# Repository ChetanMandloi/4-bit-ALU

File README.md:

# 4-bit-ALU
A simple design to perform basic logical operations (such as logical AND, OR, NOT, Addition, Subtraction and Multiplication) on two 4 bit variables using DIY PCB fabrication and assembly methods.

KiCad files to allow you to make a 4 bit ALU using Double sided copper clad board.
Pictures and instructions incoming soon.

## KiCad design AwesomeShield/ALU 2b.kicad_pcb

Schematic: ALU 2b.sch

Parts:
BT1: Battery_Cell; Pin_Header_Straight_1x02_Pitch2.54mm
D1, D2, D3, D4, D5, D6, D7, D8, D9, D10, D11, D12, D13, D14, D15, D16, D17, D18, D19, D20, D21, D22, D23, D24, D25, D26, D27, D28, D29, D30, D31, D32, D33, D34, D35: LED; LED_1206
J1, J2, J6: CONN_01X04; Pin_Header_Straight_1x04_Pitch2.54mm
J3: CONN_01X03; Pin_Header_Straight_1x03_Pitch2.54mm
J4: CONN_01X08; Pin_Header_Straight_1x08_Pitch2.54mm
J5: CONN_01X01; Pin_Header_Straight_1x01_Pitch2.54mm
R1, R2, R3, R4, R5, R6, R7, R8, R9, R10, R11, R12, R13, R14, R15, R16, R17, R18, R19, R20, R21, R22, R23, R24, R25, R26, R28: R; R_1206
U1, U2, U3: 74LS08; DIP-14_W7.62mm_Socket_LongPads
U4, U5, U6: 74LS83; DIP-16_W7.62mm_Socket_LongPads
U7: 74LS244; DIP-20_W7.62mm_Socket_LongPads
U8, U9, U10: LM741; DIP-8_W7.62mm_Socket_LongPads

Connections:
/Control_Pin_from_Board_1: U6.15, U7.15
/Data_A: BT1.2 (-), D1.1 (K), D2.1 (K), D3.1 (K), D4.1 (K), D5.1 (K), D6.1 (K), D7.1 (K), D8.1 (K), D9.1 (K), D10.1 (K), D11.1 (K), D20.1 (K), D21.1 (K), D22.1 (K), D23.1 (K), D24.1 (K), D25.1 (K), D26.1 (K), D27.1 (K), R20.2, R21.2, R22.2, R23.2, R24.2, R25.2, R26.2, R28.2, U1.7, U2.7, U3.7, U4.12, U5.12, U6.12, U7.10
unnamed: BT1.1 (+), D12.2 (A), D13.2 (A), D14.2 (A), D15.2 (A), D16.2 (A), D17.2 (A), D18.2 (A), D19.2 (A), D28.2 (A), D29.2 (A), D30.2 (A), D31.2 (A), D32.2 (A), D33.2 (A), D34.2 (A), D35.2 (A), U1.14, U2.14, U3.14, U4.5, U5.5, U6.5, U7.20, U8.1, U8.2 (-), U8.3 (+), U8.4 (V-), U9.1, U9.2 (-), U9.3 (+), U9.4 (V-), U10.2 (-), U10.3 (+), U10.4 (V-)
unnamed: D1.2 (A), D12.1 (K), R1.2
unnamed: D9.2 (A), R5.2
unnamed: D10.2 (A), R6.2
unnamed: D11.2 (A), R7.2
unnamed: D2.2 (A), D13.1 (K), R2.2
unnamed: D3.2 (A), D14.1 (K), R3.2
unnamed: D4.2 (A), D15.1 (K), R4.2
unnamed: D5.2 (A), D16.1 (K), R8.2
unnamed: D6.2 (A), D17.1 (K), R9.2
unnamed: D7.2 (A), D18.1 (K), R10.2
unnamed: D8.2 (A), D19.1 (K), R11.2
unnamed: D20.2 (A), D28.1 (K), R19.2
unnamed: D21.2 (A), D29.1 (K), R18.2
unnamed: D22.2 (A), D30.1 (K), R17.2
unnamed: D23.2 (A), D31.1 (K), R16.2
unnamed: D24.2 (A), D32.1 (K), R15.2
unnamed: D25.2 (A), D33.1 (K), R14.2
unnamed: D26.2 (A), D34.1 (K), R13.2
unnamed: D27.2 (A), D35.1 (K), R12.2
unnamed: J1.1, R4.1, R23.1, U1.13, U2.10, U3.5, U8.5
unnamed: J1.2, R3.1, R22.1, U1.2, U2.13, U3.10, U8.6
unnamed: J1.3, R2.1, R21.1, U1.5, U2.2, U3.13, U8.7 (V+)
unnamed: J1.4, R1.1, R20.1, U1.10, U2.5, U3.2, U8.8 (NC)
unnamed: J2.1, R11.1, R28.1, U1.1, U1.4, U1.9, U9.5
unnamed: J2.2, R10.1, R26.1, U1.12, U2.1, U2.4, U9.6
unnamed: J2.3, R9.1, R25.1, U2.9, U2.12, U3.1, U9.7 (V+)
unnamed: J2.4, R8.1, R24.1, U3.4, U3.9, U3.12, U9.8 (NC)
unnamed: J3.1, R5.1, U10.7 (V+)
unnamed: J3.2, R6.1, U10.6
unnamed: J3.3, R7.1, U10.5
unnamed: J4.1, R12.1, U7.18
unnamed: J4.2, R13.1, U7.16
unnamed: J4.3, R14.1, U7.14
unnamed: J4.4, R15.1, U7.12
unnamed: J4.5, R16.1, U7.9
unnamed: J4.6, R17.1, U7.7
unnamed: J4.7, R18.1, U7.5
unnamed: J4.8, R19.1, U7.3
unnamed: J5.1, U7.1, U7.19
unnamed: J6.1, U7.2
unnamed: J6.2, U4.7
unnamed: J6.3, U5.4
unnamed: J6.4, U6.16
unnamed: U1.3, U4.10
unnamed: U1.6, U4.8
unnamed: U1.8, U4.3
unnamed: U1.11, U4.11
unnamed: U2.3, U4.4
unnamed: U2.6, U4.16
unnamed: U2.8, U5.11
unnamed: U2.11, U5.7
unnamed: U3.3, U5.16
unnamed: U3.6, U6.11
unnamed: U3.8, U6.7
unnamed: U3.11, U6.4
unnamed: U4.1, U4.13, U5.13, U6.13
unnamed: U4.2, U5.8
unnamed: U4.6, U5.10
unnamed: U4.9, U7.4
unnamed: U4.14, U5.1
unnamed: U4.15, U5.3
unnamed: U5.2, U6.8
unnamed: U5.6, U6.10
unnamed: U5.9, U7.6
unnamed: U5.14, U6.1
unnamed: U5.15, U6.3
unnamed: U6.2, U7.13
unnamed: U6.6, U7.11
unnamed: U6.9, U7.8
unnamed: U6.14, U7.17

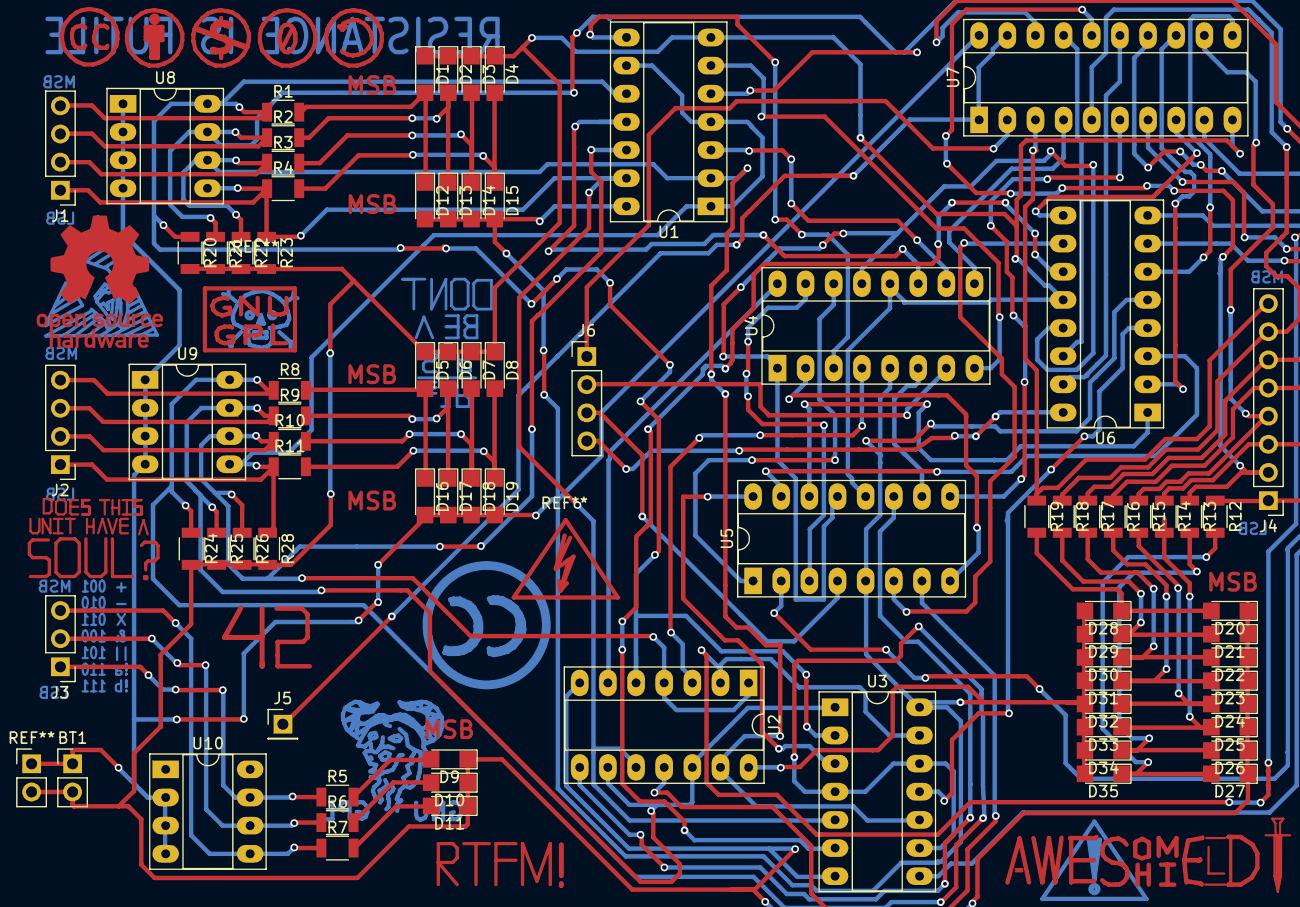
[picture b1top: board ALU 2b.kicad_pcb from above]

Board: 2 copper layers, 79 parts (0 on the bottom side), 73 nets.

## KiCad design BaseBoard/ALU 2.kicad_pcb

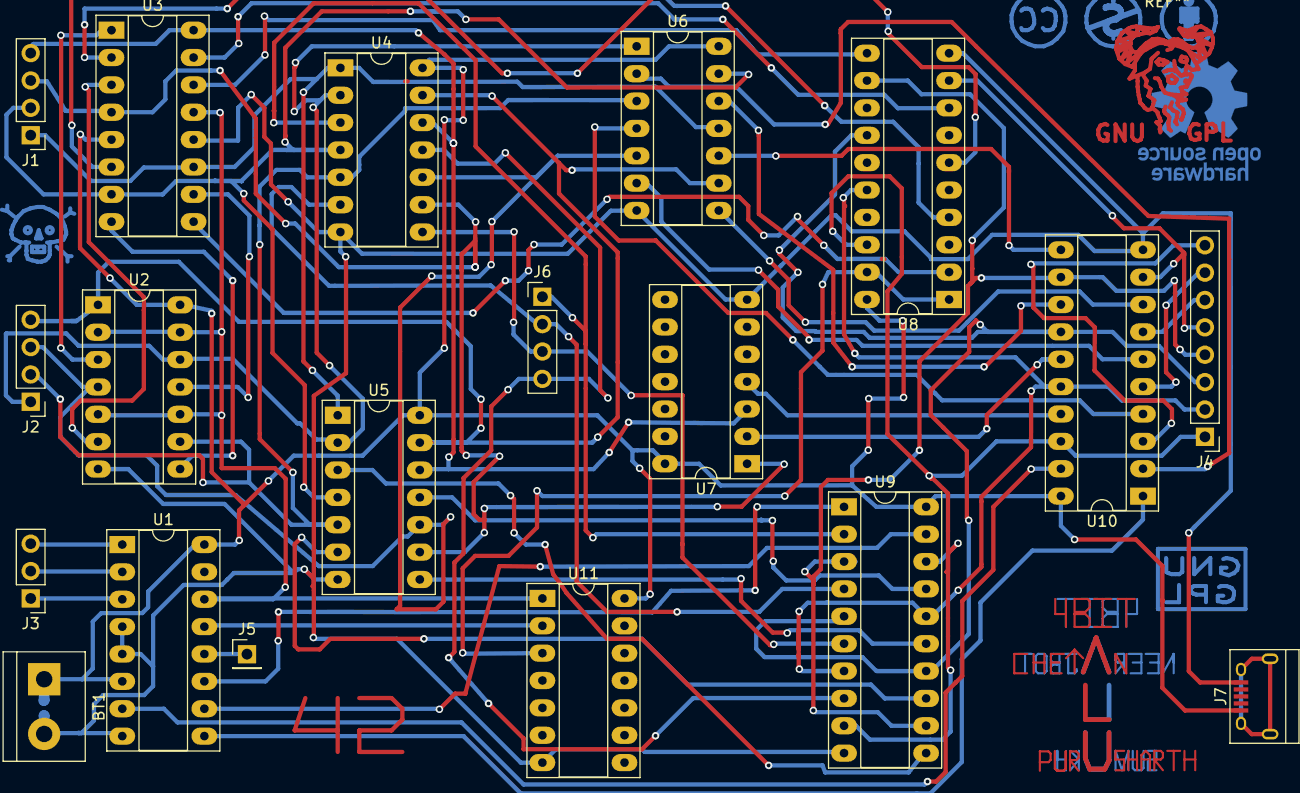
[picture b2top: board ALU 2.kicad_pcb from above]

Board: 2 copper layers, 19 parts (0 on the bottom side), 54 nets.

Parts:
BT1: Battery_Cell; bornier2
J1, J2, J6: CONN_01X04; Pin_Header_Straight_1x04_Pitch2.54mm
J3: CONN_01X03; Pin_Header_Straight_1x03_Pitch2.54mm
J4: CONN_01X08; Pin_Header_Straight_1x08_Pitch2.54mm
J5: CONN_01X01; Pin_Header_Straight_1x01_Pitch2.54mm
J7: USB_OTG; USB_Micro-B
U1: 74LS138; DIP-16_W7.62mm_Socket_LongPads
U2: 74LS86; DIP-14_W7.62mm_Socket_LongPads
U3: 74LS83; DIP-16_W7.62mm_Socket_LongPads
U4, U11: 74LS08; DIP-14_W7.62mm_Socket_LongPads
U5: 74LS32; DIP-14_W7.62mm_Socket_LongPads
U6, U7: 74LS04; DIP-14_W7.62mm_Socket_LongPads
U8, U9, U10: 74LS244; DIP-20_W7.62mm_Socket_LongPads

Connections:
/A2B2: BT1.2, J7.5, U1.4, U1.5, U1.8, U2.7, U3.12, U4.7, U5.7, U6.7, U7.7, U8.10, U9.10, U10.10, U11.7
unnamed: BT1.1, J7.1, U1.6, U1.16, U2.14, U3.5, U4.14, U5.14, U6.14, U7.14, U8.20, U9.20, U10.20, U11.14
unnamed: J1.1, U3.11, U4.1, U5.1, U6.11
unnamed: J1.2, U3.7, U4.4, U5.4, U6.13
unnamed: J1.3, U3.4, U4.9, U5.9, U7.1
unnamed: J1.4, U3.16, U4.12, U5.12, U7.3
unnamed: J2.1, U2.12, U4.2, U5.2, U6.1
unnamed: J2.2, U2.9, U4.5, U5.5, U6.3
unnamed: J2.3, U2.4, U4.10, U5.10, U6.5
unnamed: J2.4, U2.1, U4.13, U5.13, U6.9
unnamed: J3.1, U1.3
unnamed: J3.2, U1.2
unnamed: J3.3, U1.1
unnamed: J4.1, U8.18, U9.9, U9.18, U10.18
unnamed: J4.2, U8.16, U9.7, U9.16, U10.16
unnamed: J4.3, U8.14, U9.5, U9.14, U10.14
unnamed: J4.4, U8.12, U9.3, U9.12, U10.12
unnamed: J4.5, U8.9, U10.9
unnamed: J4.6, U10.7
unnamed: J4.7, U10.5
unnamed: J4.8, U10.3
unnamed: J5.1, U1.12
unnamed: J6.1, U4.3, U9.2
unnamed: J6.2, U4.6, U9.4
unnamed: J6.3, U4.8, U9.6
unnamed: J6.4, U4.11, U9.8
unnamed: U1.7, U10.19
unnamed: U1.9, U10.1
unnamed: U1.10, U9.19
unnamed: U1.11, U9.1
unnamed: U1.13, U11.2
unnamed: U1.14, U2.2, U2.5, U2.10, U2.13, U3.13, U11.1
unnamed: U2.3, U3.1
unnamed: U2.6, U3.3
unnamed: U2.8, U3.8
unnamed: U2.11, U3.10
unnamed: U3.2, U8.6
unnamed: U3.6, U8.4
unnamed: U3.9, U8.2
unnamed: U3.14, U8.11
unnamed: U3.15, U8.8
unnamed: U5.3, U9.11
unnamed: U5.6, U9.13
unnamed: U5.8, U9.15
unnamed: U5.11, U9.17
unnamed: U6.2, U10.2
unnamed: U6.4, U10.4
unnamed: U6.6, U10.6
unnamed: U6.8, U10.8
unnamed: U6.10, U10.11
unnamed: U6.12, U10.13
unnamed: U7.2, U10.15
unnamed: U7.4, U10.17
unnamed: U8.1, U8.19, U11.3

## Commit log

2018-03-07 First edition
    first iteration of base
2018-03-07 Fixed Fab Issues Pointed out by Neeraj
2018-03-07 First shield iteration
2018-03-07 Added pcb file for shield
    Assigned remaining footprints and made first layout iteration
2018-03-07 Moved footprints away from the pads in layout
2018-03-07 Moved the via under the ICs
    Vias under the IC were causing short as discovered upon fabrication of the board.
2018-03-11 Final Design
    Final design of both base and shield board which is ready to roll.
2018-03-11 Added placeholders for images and instructions
2018-03-11 Created License
2020-07-29 4 bit ALU base module after ink transfer
2020-08-08 ALU base module after etching the copper clad
